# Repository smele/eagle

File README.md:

# Personal projects and creations elaborated with Eagle.

Please remind to respect license to help others. *Respect Human Being*.

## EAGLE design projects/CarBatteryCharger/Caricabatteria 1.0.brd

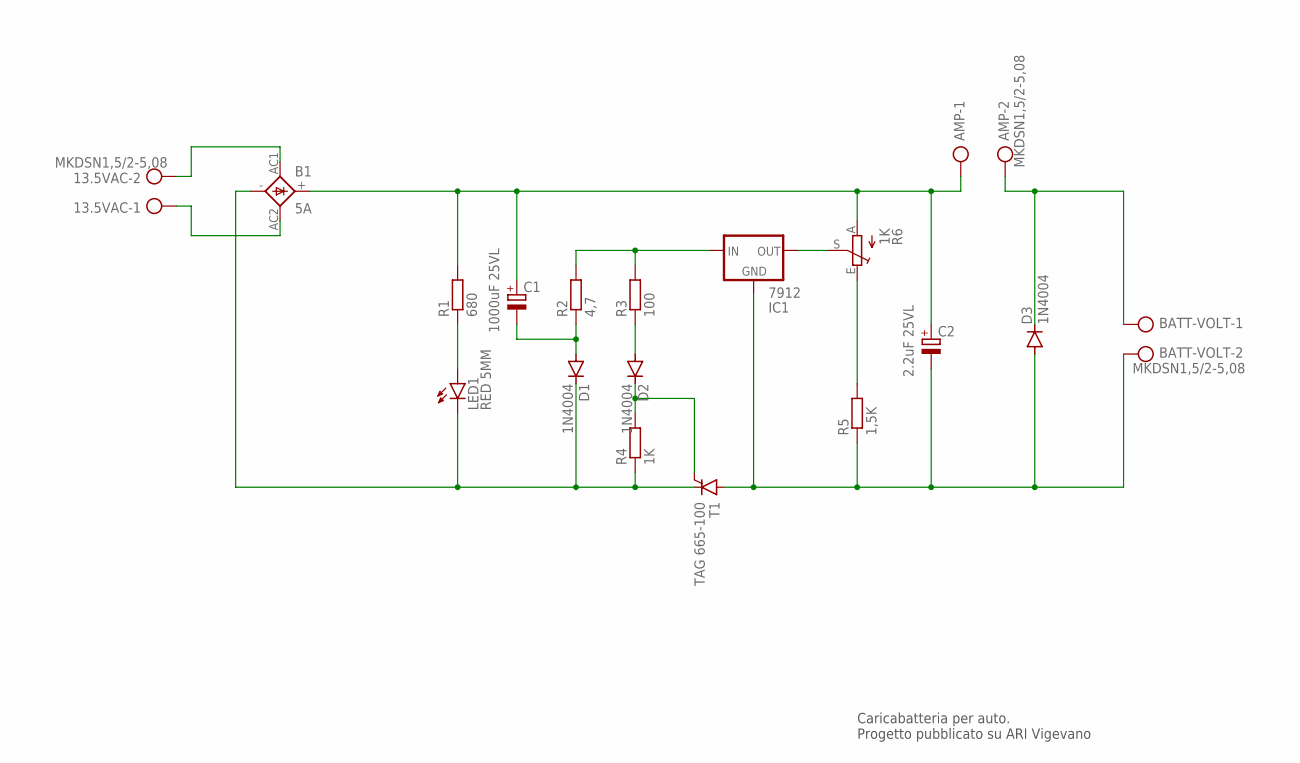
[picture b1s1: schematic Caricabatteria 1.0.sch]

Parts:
13.5VAC: MKDSN1,5/2-5,08
AMP: MKDSN1,5/2-5,08
B1: 5A; SKB
BATT-VOLT: MKDSN1,5/2-5,08
C1: 1000uF 25VL; E5-10,5
C2: 2.2uF 25VL; E5-10,5
D1, D2, D3: 1N4004; DO41-10
IC1: 7912; 79XXS
LED1: RED 5MM; LED5MM
R1: 680; 0207/10
R2: 4,7; 0207/10
R3: 100; 0207/10
R4: 1K; 0207/10
R5: 1,5K; 0207/10
R6: 1K; PT-10S
T1: TAG 665-100; TOP3S-2

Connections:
unnamed: C1.-, D1.A, R2.1
unnamed: LED1.A, R1.1
unnamed: AMP.2, BATT-VOLT.1, D3.C
unnamed: D2.A, R3.1
unnamed: D2.C, R4.2, T1.G
unnamed: IC1.IN, R2.2, R3.2
unnamed: B1.-, D1.C, LED1.K (C), R4.1, T1.C
unnamed: BATT-VOLT.2, C2.-, D3.A, IC1.GND, R5.1, T1.A
unnamed: IC1.OUT, R6.S
unnamed: R5.2, R6.E
unnamed: AMP.1, B1.+, C1.+, C2.+, R1.2, R6.A
unnamed: 13.5VAC.2, B1.AC1
unnamed: 13.5VAC.1, B1.AC2

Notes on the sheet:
Caricabatteria per auto. Progetto pubblicato su ARI Vigevano

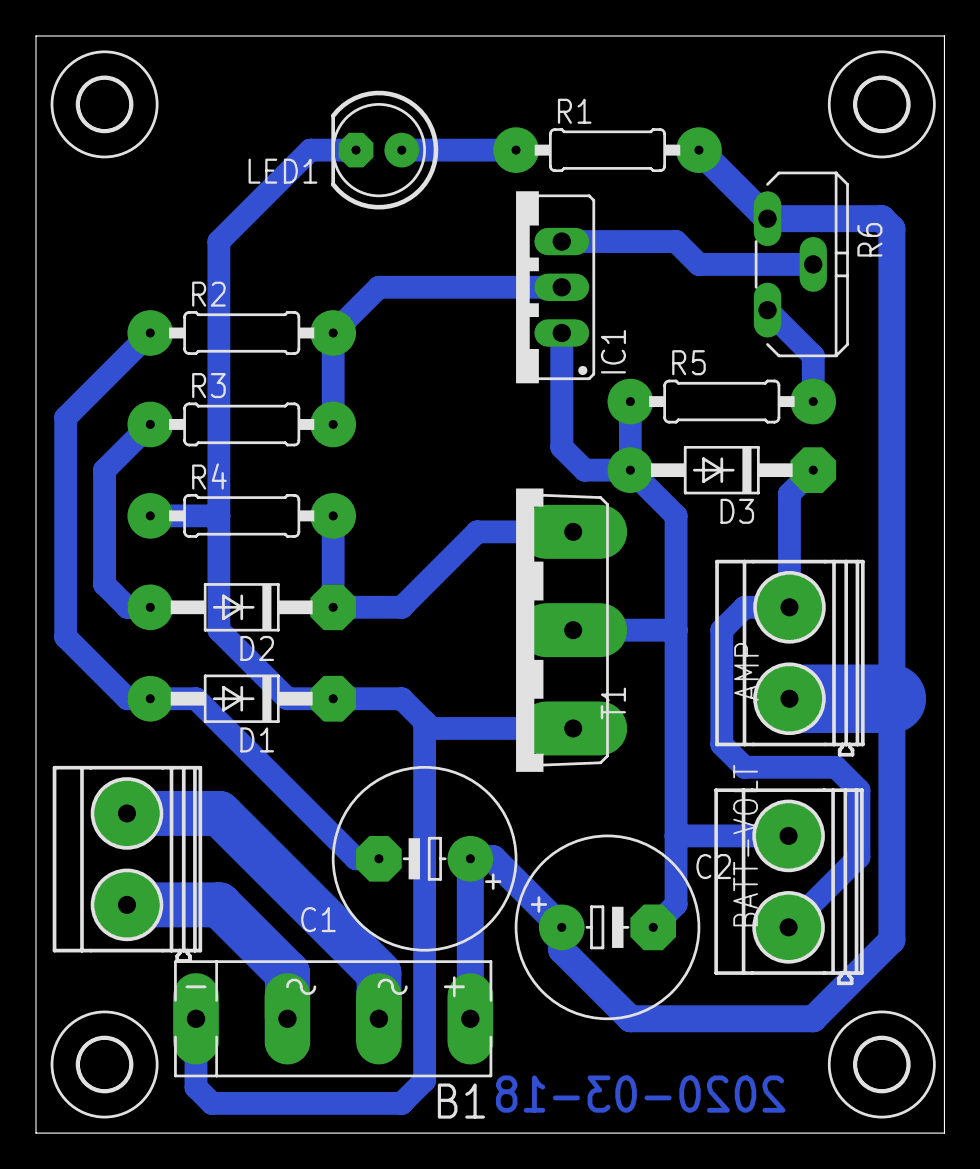
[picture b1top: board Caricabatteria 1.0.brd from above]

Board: 2 copper layers, 50.5 x 61.0 mm, 22 parts (0 on the bottom side), 13 nets.

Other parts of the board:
U$1, U$2, U$3, U$4: 2,8

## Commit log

2020-03-18 First Commit
    Some libraries modified with robust pads for better solder and resistant works.
2020-03-18 Deleted backup files
    Deleted backup files
2020-03-18 Some detail adjust.
    Some detail adjust.
2020-03-18 Correct value of some component
2020-04-01 TRIAC BTW68 pad modification
    Added TRIAC library with pad BTW68, TOP3 Package modification
2020-04-01 Added 74xx library with modifications
    Added 74xx library with modifications on Vcc and GND pin . Not necessary INVOKE command to visualize power supply pins.
2020-04-01 Power Supply Connected.
    Power Supply Connected on PCB
2020-04-01 Backup files erased
    Backup files erased
2020-04-01 Tweak of PCB
    Tweak of PCB
